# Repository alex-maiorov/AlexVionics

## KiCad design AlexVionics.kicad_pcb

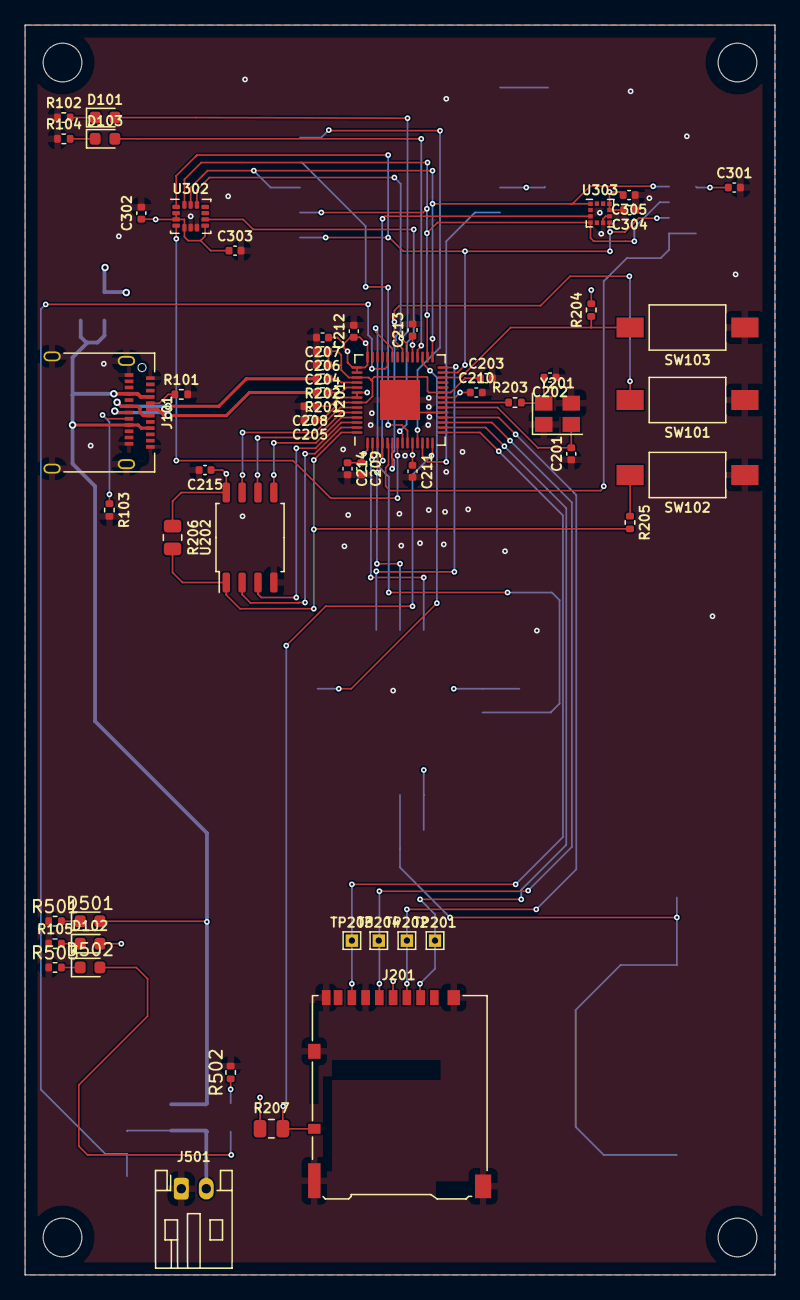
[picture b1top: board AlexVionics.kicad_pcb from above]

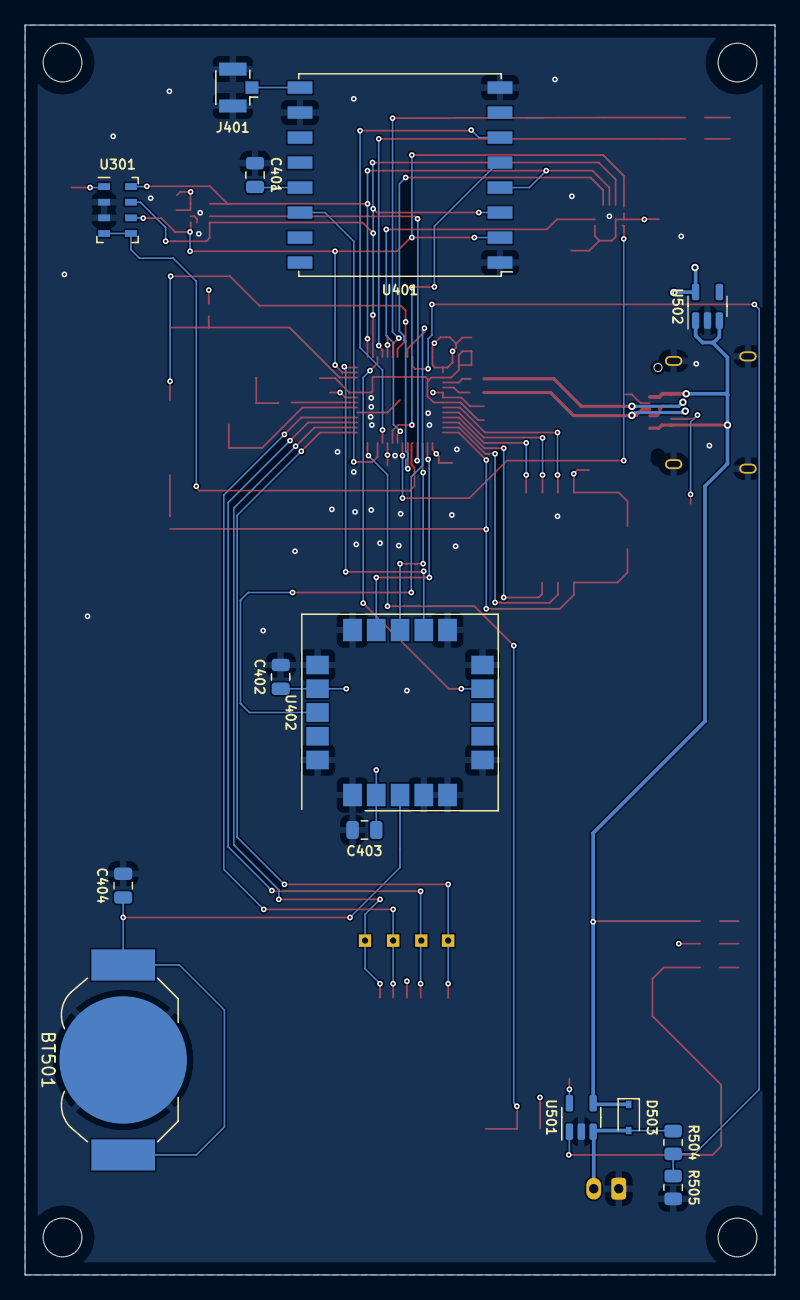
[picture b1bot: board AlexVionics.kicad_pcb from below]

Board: 4 copper layers, 60.0 x 100.0 mm, 69 parts (14 on the bottom side), 56 nets.

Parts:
BT501: Battery_Cell; BatteryHolder_LINX_BAT-HLD-012-SMT
C201, C202: 10p; C_0402_1005Metric
C203, C204, C205, C208, C209, C210, C211, C212, C213, C214, C215, C301, C302, C303, C304, C305: 100n; C_0402_1005Metric
C206, C207: 1u; C_0402_1005Metric
C401, C403: 1u; C_0805_2012Metric
C402, C404: 100n; C_0805_2012Metric
D101: GREEN; LED_0603_1608Metric
D102: WHITE; LED_0603_1608Metric
D103: BLUE; LED_0603_1608Metric
D501: RED; LED_0603_1608Metric
D502: YELLOW; LED_0603_1608Metric
D503: D; D_SOD-323
J101: USB_C_Receptacle_USB2.0; USB_C_Receptacle_Amphenol_12401610E4-2A
J201: Micro_SD_Card_Det; microSD_HC_Hirose_DM3AT-SF-PEJM5
J401: u.FL; U.FL_Hirose_U.FL-R-SMT-1_Vertical
J501: Conn_01x02; JST_PH_S2B-PH-K_1x02_P2.00mm_Horizontal
R101, R103: 5.1k; R_0402_1005Metric
R102, R104, R105: 470; R_0402_1005Metric
R201, R202: 33; R_0402_1005Metric
R203, R205, R501, R503: 1k; R_0402_1005Metric
R204, R502: 10k; R_0402_1005Metric
R206: DNF; R_0805_2012Metric
R207: 10k; R_0805_2012Metric
R504, R505: 100k; R_0805_2012Metric
SW101, SW102, SW103: PTS636; SW_SPST_FSMSM
TP201: SD_CS; TestPoint_THTPad_1.0x1.0mm_Drill0.5mm
TP202: SPI1_SDO; TestPoint_THTPad_1.0x1.0mm_Drill0.5mm
TP203: SPI1_SDI; TestPoint_THTPad_1.0x1.0mm_Drill0.5mm
TP204: SPI1_SCK; TestPoint_THTPad_1.0x1.0mm_Drill0.5mm
U201: RP2040; QFN-56-1EP_7x7mm_P0.4mm_EP3.2x3.2mm
U202: W25Q128JVS; SOIC-8_5.23x5.23mm_P1.27mm
U301: MS5611-01BA; LGA-8_3x5mm_P1.25mm
U302: LSM6DS3; LGA-14_3x2.5mm_P0.5mm_LayoutBorder3x4y
U303: LIS2MDL; LGA-12_2x2mm_P0.5mm
U401: RFM96W-433S2; HOPERF_RFM9XW_SMD
U402: SAM-M8Q; ublox_SAM-M8Q
U501: MCP73831-2-OT; SOT-23-5
U502: AP2127K-3.3; SOT-23-5
Y201: Crystal_GND24; Crystal_SMD_3225-4Pin_3.2x2.5mm

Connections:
+1V1: C203.1, C204.1, C205.1, C206.1, U201.23 (DVDD), U201.45 (VREG_VOUT), U201.50 (DVDD)
+3V0: BT501.1 (+), C404.1, U402.3 (V_BCKP)
+3V3: C207.1, C208.1, C209.1, C210.1, C211.1, C212.1, C213.1, C214.1, C215.1, C301.1, C302.1, C303.1, C304.2, C305.2, C401.2, C402.1, C403.1, D102.2 (A), J201.4 (VDD), R204.2, R206.1, R207.1, U201.1 (IOVDD), U201.10 (IOVDD), U201.22 (IOVDD), U201.33 (IOVDD), U201.42 (IOVDD), U201.43 (ADC_AVDD), U201.44 (VREG_IN), U201.48 (USB_VDD), U201.49 (IOVDD), U202.8 (VCC), U301.1 (VDD), U302.2 (SDX), U302.3 (SCX), U302.5 (VDDIO), U302.8 (VDD), U303.9 (VDD), U303.10 (VDDIO), U401.13 (3.3V), U402.2 (VCC_IO), U402.17 (VCC), U502.5 (VOUT)
+BATT: D503.2 (A), J501.2, R504.1, U501.3 (VBAT)
/MCU/A0: R504.2, R505.1, U201.38 (GPIO26_ADC0)
/MCU/GPIO2: U201.4 (GPIO2), U303.3 (CS)
/MCU/GPIO3: U201.5 (GPIO3), U301.4 (CSB), U301.5 (CSB)
/MCU/GPIO4: U201.6 (GPIO4), U302.12 (CS)
/MCU/GPIO5: U201.7 (GPIO5), U302.4 (INT1)
/MCU/GPIO6: U201.8 (GPIO6), U302.9 (INT2)
/MCU/GPIO7: U201.9 (GPIO7), U401.5 (NSS)
/MCU/GPIO8: U201.11 (GPIO8), U401.6 (RESET)
/MCU/GPIO9: U201.12 (GPIO9), U401.14 (DIO0)
/MCU/GPIO21: D103.2 (A), U201.32 (GPIO21)
/MCU/GPIO22: D101.2 (A), U201.34 (GPIO22)
/MCU/GPIO23: SW101.2, U201.35 (GPIO23)
/MCU/GPIO25: U201.37 (GPIO25), U402.18 (~RESET)
/MCU/I2C0_SCL: U201.28 (GPIO17), U402.12 (SCL)
/MCU/I2C0_SDA: U201.31 (GPIO20), U402.9 (SDA)
/MCU/QSPI_CS: R205.2, R206.2, U201.56 (QSPI_SS), U202.1 (~CS)
/MCU/QSPI_IO0: U201.53 (QSPI_SD0), U202.5 (DI(IO0))
/MCU/QSPI_IO1: U201.55 (QSPI_SD1), U202.2 (DO(IO1))
/MCU/QSPI_IO2: U201.54 (QSPI_SD2), U202.3 (IO2)
/MCU/QSPI_IO3: U201.51 (QSPI_SD3), U202.7 (IO3)
/MCU/QSPI_SCK: U201.52 (QSPI_SCLK), U202.6 (CLK)
/MCU/RESET: R204.1, SW103.2, U201.26 (RUN)
/MCU/SD_CS: J201.2 (DAT3/CD), TP201.1, U201.16 (GPIO13)
/MCU/SPI0_SCK: U201.29 (GPIO18), U301.8 (SCLK), U302.13 (SCL), U303.1 (SCL/SPC), U401.4 (SCK)
/MCU/SPI0_SDI: U201.27 (GPIO16), U301.6 (SDO), U302.1 (SDO/SA0), U303.7 (INT/DRDY/SDO), U401.2 (MISO)
/MCU/SPI0_SDO: U201.30 (GPIO19), U301.7 (SDI/SDA), U302.14 (SDA), U303.4 (SDA/SDI/SDO), U401.3 (MOSI)
/MCU/SPI1_SCK: J201.5 (CLK), TP204.1, U201.17 (GPIO14)
/MCU/SPI1_SDI: J201.7 (DAT0), TP203.1, U201.15 (GPIO12)
/MCU/SPI1_SDO: J201.3 (CMD), TP202.1, U201.18 (GPIO15)
/MCU/UART0_RX: U201.3 (GPIO1), U402.13 (TXD)
/MCU/UART0_TX: U201.2 (GPIO0), U402.14 (RXD)
/MCU/USB_BOOT: R205.1, SW102.2
/MCU/USB_DM: J101.A7 (D-), J101.B7 (D-), R202.2
/MCU/USB_DP: J101.A6 (D+), J101.B6 (D+), R201.2
/MCU/~SD_DET: J201.10 (DET_A), R207.2, U201.14 (GPIO11)
GND: BT501.2 (-), C201.1, C202.1, C203.2, C204.2, C205.2, C206.2, C207.2, C208.2, C209.2, C210.2, C211.2, C212.2, C213.2, C214.2, C215.2, C301.2, C302.2, C303.2, C304.1, C305.1, C401.1, C402.2, C403.2, C404.2, J101.A1 (GND), J101.A12 (GND), J101.B1 (GND), J101.B12 (GND), J101.S1 (SHIELD), J201.6 (VSS), J201.9 (DET_B), J201.11 (SHIELD), J401.2 (Ext), J501.1, R101.2, R102.1, R103.2, R104.1, R105.1, R501.1, R502.2, R503.1, R505.2, SW101.1, SW102.1, SW103.1, U201.19 (TESTEN), U201.57 (GND), U202.4 (GND), U301.2 (PS), U301.3 (GND), U302.6 (GND), U302.7 (GND), U303.6 (GND), U303.8 (GND), U401.1 (GND), U401.8 (GND), U401.10 (GND), U402.1 (GND), U402.4 (GND), U402.5 (GND), U402.6 (GND), U402.10 (GND), U402.11 (GND), U402.15 (GND), U402.16 (GND), U402.20 (GND), U501.2 (VSS), U502.2 (GND), Y201.1, Y201.3
unnamed: C201.2, U201.20 (XIN), Y201.2
unnamed: C202.2, R203.1, Y201.4
unnamed: D101.1 (K), R102.2
unnamed: D102.1 (K), R105.2
unnamed: D103.1 (K), R104.2
unnamed: D501.1 (K), R501.2
unnamed: D502.1 (K), R503.2
unnamed: D502.2 (A), U501.1 (STAT)
unnamed: J101.A5 (CC1), R101.1
unnamed: J101.B5 (CC2), R103.1
unnamed: J401.1 (In), U401.9 (ANT)
unnamed: R201.1, U201.47 (USB_DP)
unnamed: R202.1, U201.46 (USB_DM)
unnamed: R203.2, U201.21 (XOUT)
unnamed: R502.1, U501.5 (PROG)
VBUS: D501.2 (A), D503.1 (K), J101.A4 (VBUS), J101.A9 (VBUS), J101.B4 (VBUS), J101.B9 (VBUS), U501.4 (VDD), U502.1 (VIN), U502.3 (EN)

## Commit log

2022-09-09 finished telemetry
2022-09-15 Finished Snesors
2022-09-15 fixed symbol table and created POWER
2022-09-19 started connecting board
2022-12-26 finished routing
